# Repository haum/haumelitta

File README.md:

HAUMelitta
==========

HAUMelitta is a project intended to connect a coffeepot to the Internet through a Twitter account.

It's our modest contribution to the Web of objects.

Why this name ?
---------------

The name is a contraction of HAUM (our hackerspace) and Melitta (well-known coffepot manufacturer).

How does it work ?
-------------------

The coffeepot has its own Twitter account (@HAUMelitta) and API tokens/secrets have been generated to get updates on the
Pi.

When a tweet containing the right keyword is emitted from one of the masters, the Pi commutes a static relay that switches
on the coffeepot.

Requirements
------------

Here's what you need...

### Bill of material

- A RaspberryPi (tested on raspbian)
- A Coffeepot
- A static relay

### Software part

You'll need several python modules, just grab the `setup.sh` script and run:

    $ sudo su
    # sudo apt-get install python3
    # ./setup.sh

Modules are:

- `wiringpi`
- `twitter`

The easiest way to get started is to create a new virtualenv then run from inside :

    $ mkvirtualenv haumelitta
    $ pip install -r requirements.txt

Running
-------

Connect your static relay to commute on pin 17 (port 1 on Pi).

Run :

    $ workon haumelitta
    $ python coffeesource.py

Control instructions will be written in the console.

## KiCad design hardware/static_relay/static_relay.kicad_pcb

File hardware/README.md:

Hardware
==========

all materials in this rep is relative to hardware part of HAUMelitta

Schematics and pcb are make with [kicad](http://www.kicad-pcb.org)

First part is a static relay

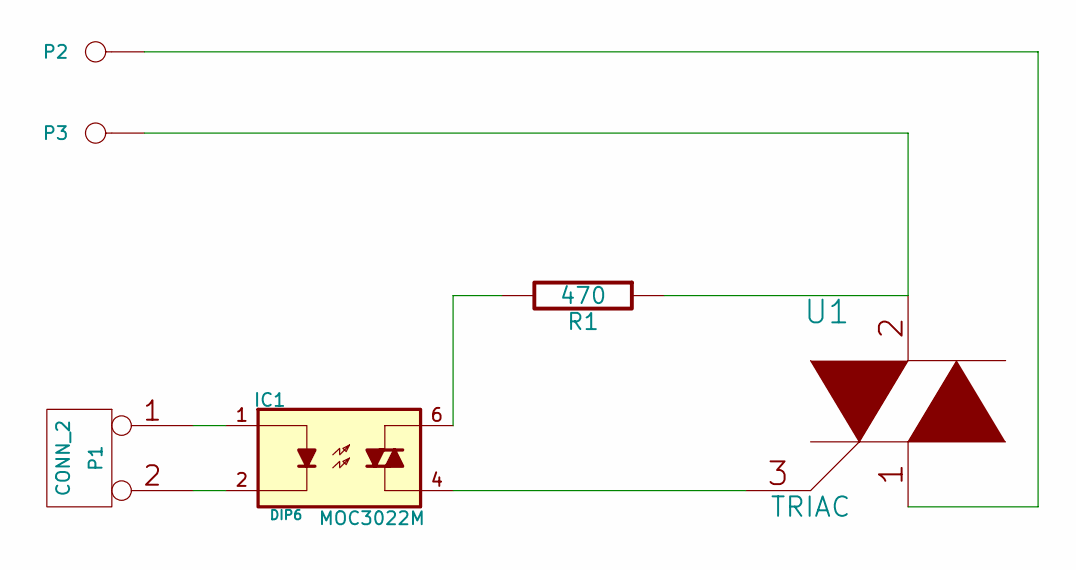
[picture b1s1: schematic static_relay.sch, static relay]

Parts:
IC1: MOC3022M; DIP6
P1: CONN_2
P2, P3: CONN_1
R1: 470
U1: TRIAC

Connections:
unnamed: IC1.2, P1.2 (PM)
unnamed: IC1.1, P1.1
unnamed: P2.1, U1.1
unnamed: P3.1, R1.1, U1.2
unnamed: IC1.6, R1.2
unnamed: IC1.4, U1.3

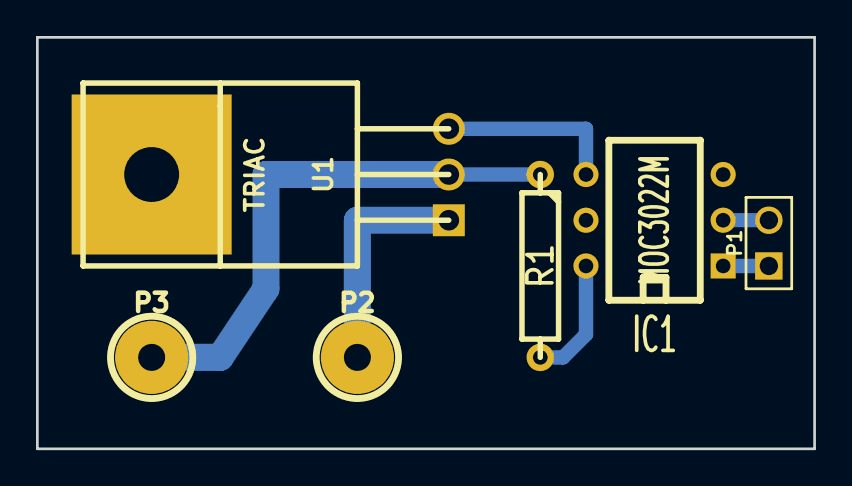
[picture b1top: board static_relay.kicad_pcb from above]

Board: 2 copper layers, 43.2 x 22.9 mm, 6 parts (0 on the bottom side), 6 nets.

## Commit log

2013-05-17 Initial import
2013-05-17 Do not track bytecode and settings
2013-05-17 Do not track bytecode
2013-05-17 Fix typos in README
2013-05-17 Separate sighandlers from core & remember last tweet
2013-05-17 Import GPIO lib in handlers
2013-05-17 Typo
2013-05-17 Rewriting using python 3
2013-05-17 Syntax error fixed :)
2013-05-17 New setup for 3k version
2013-05-17 OAuth2's not needed
2013-05-17 Rewriting to py3k
2013-05-17 back dict lookup
2013-05-17 open/close pin
2013-05-17 bad reference
2013-05-17 fix import error
2013-05-17 Rewriting
2013-05-17 Final rewriting for 3k version
2013-05-17 Update time in compliance with API rules
2013-05-18 update readme for 3k version
2013-05-19 static relay hardware added
2013-05-19 Hardware README add and hardware rep clean
2013-05-21 localIO access test
2013-05-21 hardware update
2013-05-22 pi intertace added
2013-05-22 Add requirements for venv install
2013-05-22 Ajout d'instructions pour le run
2013-05-22 Fix whitespace
2013-05-22 Ajout du fichier de base pour la version threaded
2013-05-22 Ajout de l'Handler pour twitter
2013-05-22 moar globals :)
2013-05-22 Rewrite signal handlers a bit
2013-05-22 main script
2013-05-22 Corrections
2013-05-22 Add __init__.py for imports
2013-05-22 Base for GPIO interface handler. To be continued
2013-05-23 Bug fix première session
2013-05-23 Rewrite coffee_pin as a singleton
2013-05-23 Correction
2013-05-23 test bp IO
2013-05-23 specifie utilisation bus I2C
2013-05-23 first IO handle
2013-05-23 disable twitter thread
2013-05-23 def adress of PCF8574 8-BIT I/O EXPANDER
2013-05-23 remove TABs
2013-05-23 def I2C interupt pin
2013-05-23 correct ref to lib as gpio.
2013-05-23 select name pyto correct
2013-05-23 python 3 epoll eventmask
2013-05-24 Merge
2013-05-26 may be thread progress
2013-05-26 clean up
2013-05-27 suppression ouverture concurente
2013-05-28 added a proof of concept for IO interupt
2013-05-28 correction ref
2013-05-28 mauvais copier/coller :)
2013-05-28 doigts carrés et neuronnes enbrouillés :)
2013-05-28 interrupt edge changed
2013-05-28 add PullUp on interupt pin
2013-05-28 use python3
2013-05-28 setup interrupt handler for SIGTERM
2013-05-28 correct import
2013-05-31 Correction des bugs de la version threadée des boutons
2013-05-31 Ajout d'une tempo pour l'handler twitter
2013-05-31 Ajout du module pour changer l'état de la cafetière
2013-05-31 Suppression des fichiers inutiles
2013-05-31 controle et génération du fichier de configuration
2013-05-31 mise en place structure fichier
2013-05-31 Renommage du fichier contenant les primitives à cafetière
2013-05-31 Suppression de la définition de la pin à cafetière
2013-05-31 Démarrage du thread twitter
2013-05-31 Réécriture pour utiliser les primitives de la cafetière
2013-05-31 suite structure
2013-05-31 Rangement
2013-05-31 Condition pour le check twitter
2013-05-31 flag a bit of code for deletion
2013-05-31 Ajout de la prise en compte des boutons
2013-05-31 debut ecriture
2013-06-01 Ajout de messages pour le log dans coffeepot.py
2013-06-01 Réécriture de la condition d'allumage twitter
    * Suppression de la condition d'extinction
    * Changement du message de logging
    * Réduction de la condition : double if => and
2013-06-01 esssais de try: import
2013-06-01 formatage values for setting
2013-06-02 mise en place d'un controle de chaque variable
2013-06-02 syteme de lecture / creation de fichier de config
2013-06-03 correction enregistrement variable numeriques
2016-04-10 Use wiringpi
2016-04-11 les experts miami
2016-04-14 Invert logic
2016-04-14 Inversed logic
2016-04-14 Default value
2016-04-14 Cleanup
2016-04-14 MÉNAGE
2016-04-14 Settings
2016-04-14 Display error
2016-05-15 Test FSM
